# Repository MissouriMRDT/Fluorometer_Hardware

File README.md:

# Fluorometer_Breakout_Hardware
Breakout board for CCD with serial interface

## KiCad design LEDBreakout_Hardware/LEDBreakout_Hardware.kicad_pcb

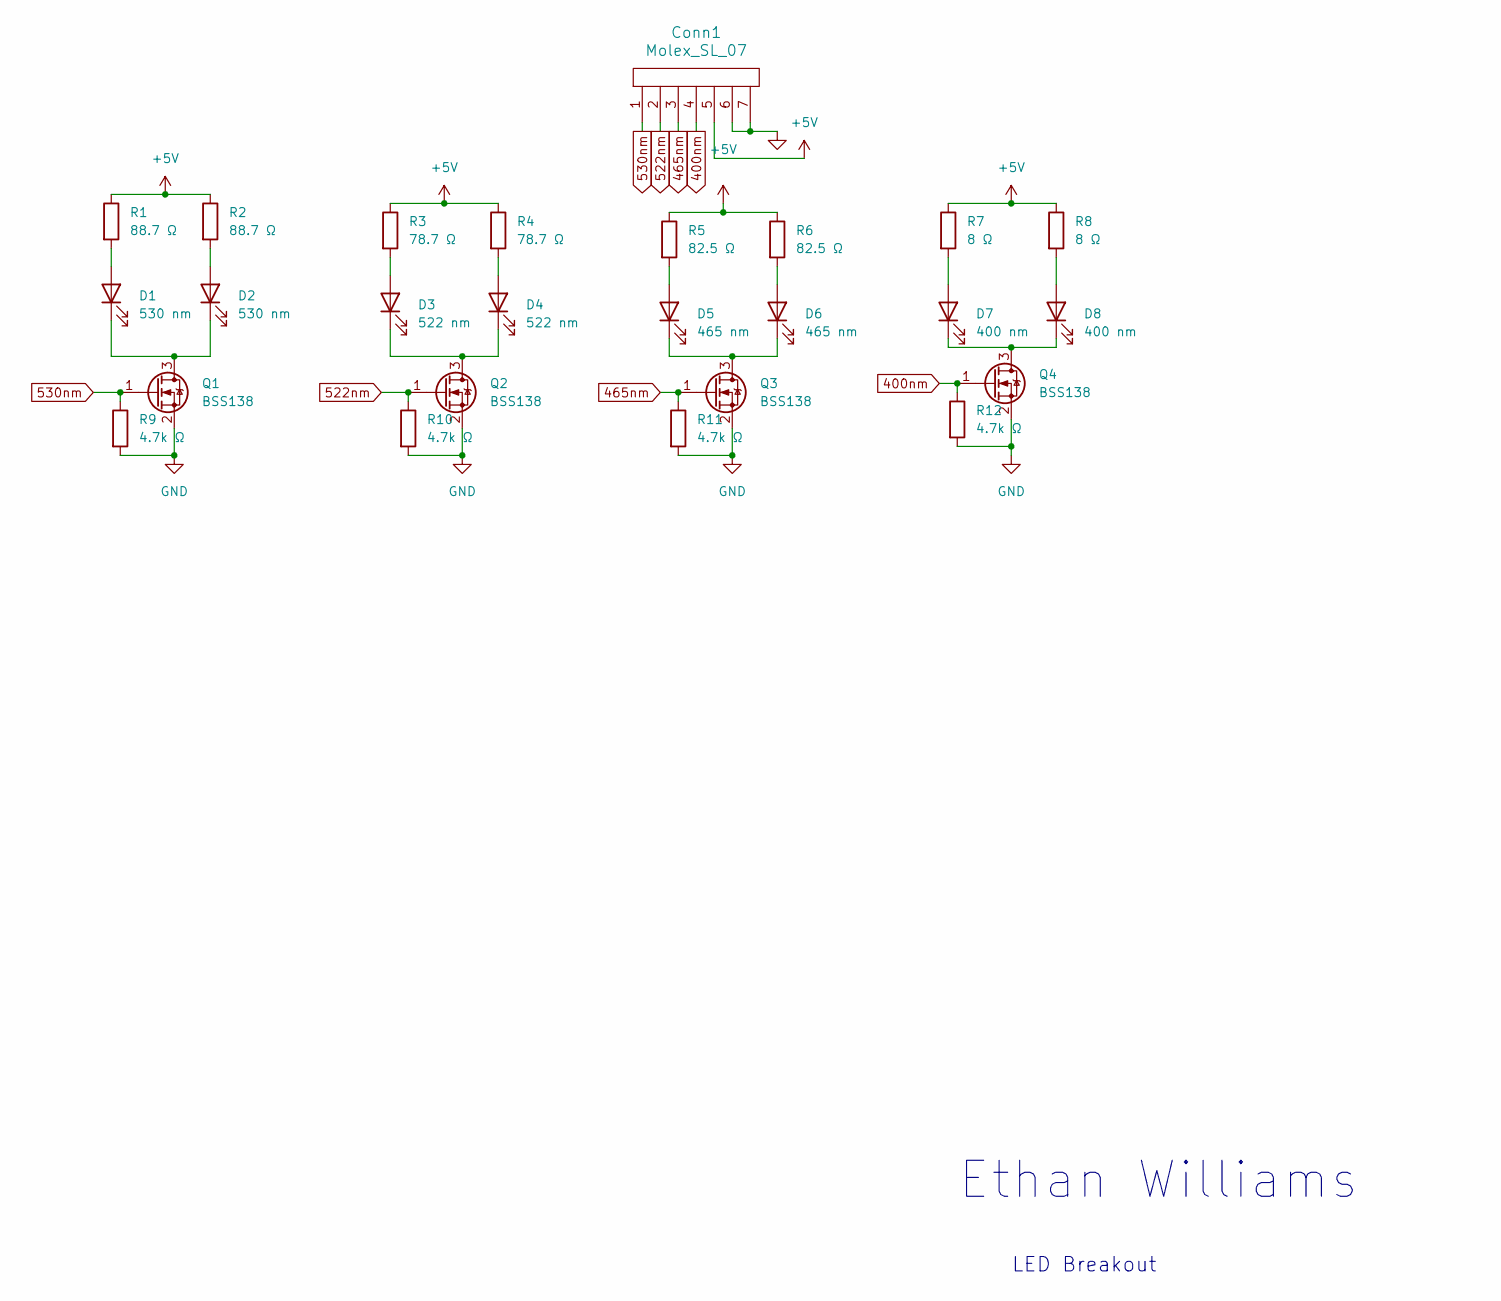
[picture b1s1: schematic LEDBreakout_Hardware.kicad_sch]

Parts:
Conn1: Molex_SL_07; MOLEX_SL_07_Vertical
D1, D2: 530 nm; D_DO-15_P2.54mm_Vertical_AnodeUp
D3, D4: 522 nm; D_DO-15_P2.54mm_Vertical_AnodeUp
D5, D6: 465 nm; D_DO-15_P2.54mm_Vertical_AnodeUp
D7, D8: 400 nm; 3528SMD_Diode
Q1, Q2, Q3, Q4: BSS138; SOT-23
R1, R2: 88.7 Ω; R_0603_1608Metric_Pad0.98x0.95mm_HandSolder
R3, R4: 78.7 Ω; R_0603_1608Metric_Pad0.98x0.95mm_HandSolder
R5, R6: 82.5 Ω; R_0603_1608Metric_Pad0.98x0.95mm_HandSolder
R7, R8: 8 Ω; R_2010_5025Metric_Pad1.40x2.65mm_HandSolder
R9, R10, R11, R12: 4.7k Ω; R_0603_1608Metric_Pad0.98x0.95mm_HandSolder

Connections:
400nm: Conn1.4, Q4.1 (G), R12.1
465nm: Conn1.3, Q3.1 (G), R11.1
522nm: Conn1.2, Q2.1 (G), R10.1
530nm: Conn1.1, Q1.1 (G), R9.1
+5V: Conn1.5, R1.1, R2.1, R3.1, R4.1, R5.1, R6.1, R7.1, R8.1
GND: Conn1.6, Conn1.7, Q1.2 (S), Q2.2 (S), Q3.2 (S), Q4.2 (S), R9.2, R10.2, R11.2, R12.2
unnamed: D1.2 (A), R1.2
unnamed: D1.1 (K), D2.1 (K), Q1.3 (D)
unnamed: D2.2 (A), R2.2
unnamed: D3.2 (A), R3.2
unnamed: D3.1 (K), D4.1 (K), Q2.3 (D)
unnamed: D4.2 (A), R4.2
unnamed: D5.2 (A), R5.2
unnamed: D5.1 (K), D6.1 (K), Q3.3 (D)
unnamed: D6.2 (A), R6.2
unnamed: D7.2 (A), R7.2
unnamed: D7.1 (K), D8.1 (K), Q4.3 (D)
unnamed: D8.2 (A), R8.2

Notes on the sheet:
LED Breakout
Ethan Williams

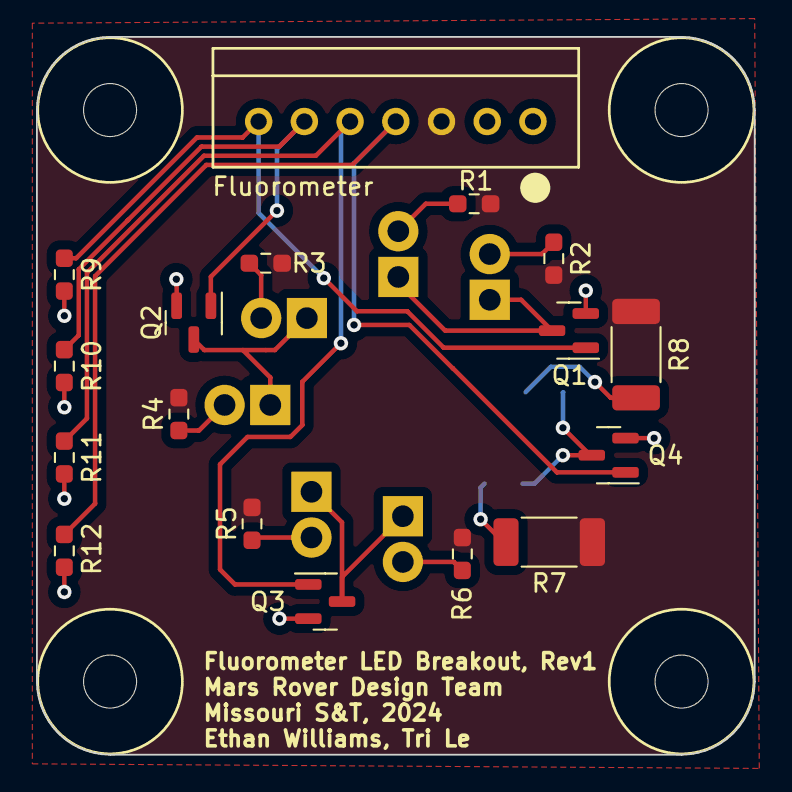
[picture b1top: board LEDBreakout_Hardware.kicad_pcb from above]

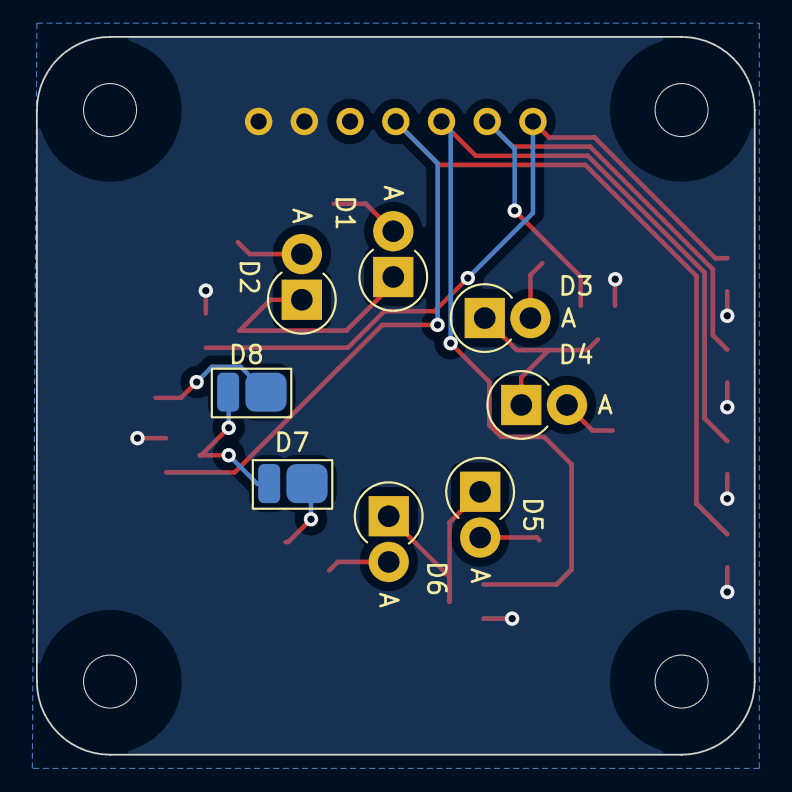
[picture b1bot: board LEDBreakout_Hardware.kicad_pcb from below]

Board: 2 copper layers, 39.9 x 39.9 mm, 25 parts (8 on the bottom side), 18 nets.

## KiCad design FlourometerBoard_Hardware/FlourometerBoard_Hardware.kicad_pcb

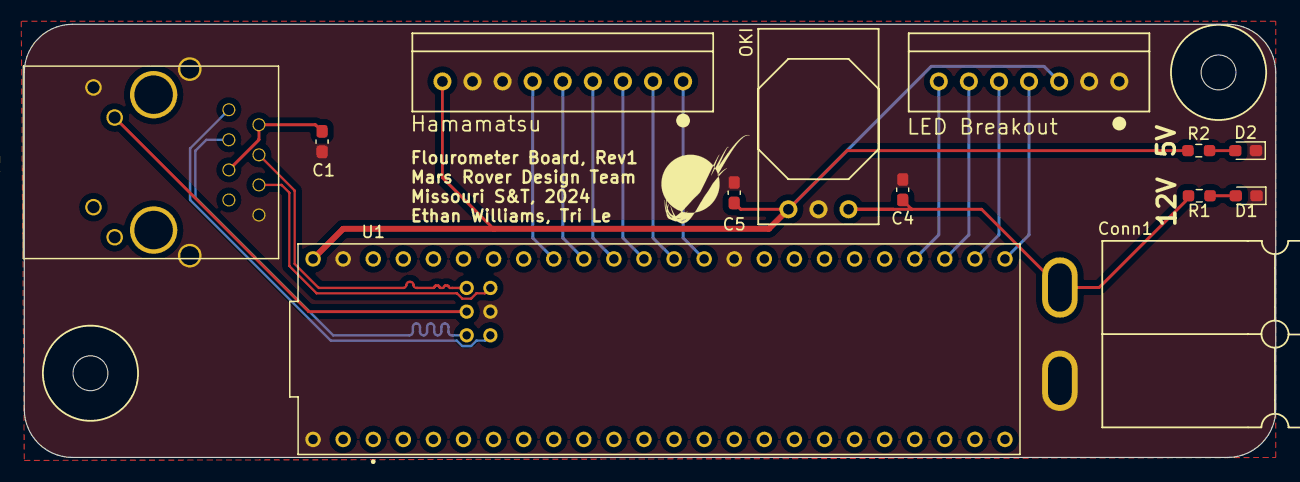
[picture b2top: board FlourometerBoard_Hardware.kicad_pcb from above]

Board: 2 copper layers, 105.7 x 36.6 mm, 13 parts (0 on the bottom side), 21 nets.

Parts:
C1: 0.1 uF; C_0603_1608Metric_Pad1.08x0.95mm_HandSolder
C4, C5: 10 uF; C_0603_1608Metric_Pad1.08x0.95mm_HandSolder
Conn1: AndersonPP; Square_Anderson_2_H_Side_By_Side
Conn2: Molex_SL_09; MOLEX_SL_09_Vertical
Conn3: Molex_SL_07; MOLEX_SL_07_Vertical
D1, D2: Green; LED_0603_1608Metric_Pad1.05x0.95mm_HandSolder
J1: RJ45_LED_Shielded; RJ45_Teensy
R1: 1000 Ω; R_0603_1608Metric_Pad0.98x0.95mm_HandSolder
R2: 100 Ω; R_0603_1608Metric_Pad0.98x0.95mm_HandSolder
U1: Teensy4.1_DEV-16771; Teensy_4_1_Ethernet
U3: OKI; OKI_Horizontal

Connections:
400nm LED: Conn3.4, U1.33 (MCLK2)
430nm LED: Conn3.3, U1.34 (RX8)
522nm LED: Conn3.2, U1.35 (TX8)
530nm LED: Conn3.1, U1.36 (CS2)
+5V: C5.1, Conn2.1, Conn3.5, R2.1, U1.VIN, U3.3 (Vo)
+12V: C4.1, Conn1.2 (V+Log), R1.1, U3.1 (Vi)
CLK: Conn2.7, U1.15 (A1)
EOS: Conn2.4, U1.18 (A4)
GND: C1.1, C4.2, C5.2, Conn1.1 (GND), Conn2.2, Conn2.3, Conn3.6, Conn3.7, D1.1 (K), D2.1 (K), J1.8, J1.9, J1.SH, U1.GND1 (GND), U1.GND2 (GND), U1.GND3 (GND), U1.GND5 (GND), U3.2 (GND)
LED: J1.10, U1.LED
unnamed: C1.2, J1.2, J1.5
unnamed: D1.2 (A), R1.2
unnamed: D2.2 (A), R2.2
R+: J1.4, U1.R+
R-: J1.6, U1.R-
START: Conn2.6, U1.16 (A2)
T+: J1.1, U1.T+
T-: J1.3, U1.T-
TRG: Conn2.5, U1.17 (A3)
VIDEO: Conn2.8, U1.14 (A0)
WHITE_LED: Conn2.9, U1.13 (SCK)

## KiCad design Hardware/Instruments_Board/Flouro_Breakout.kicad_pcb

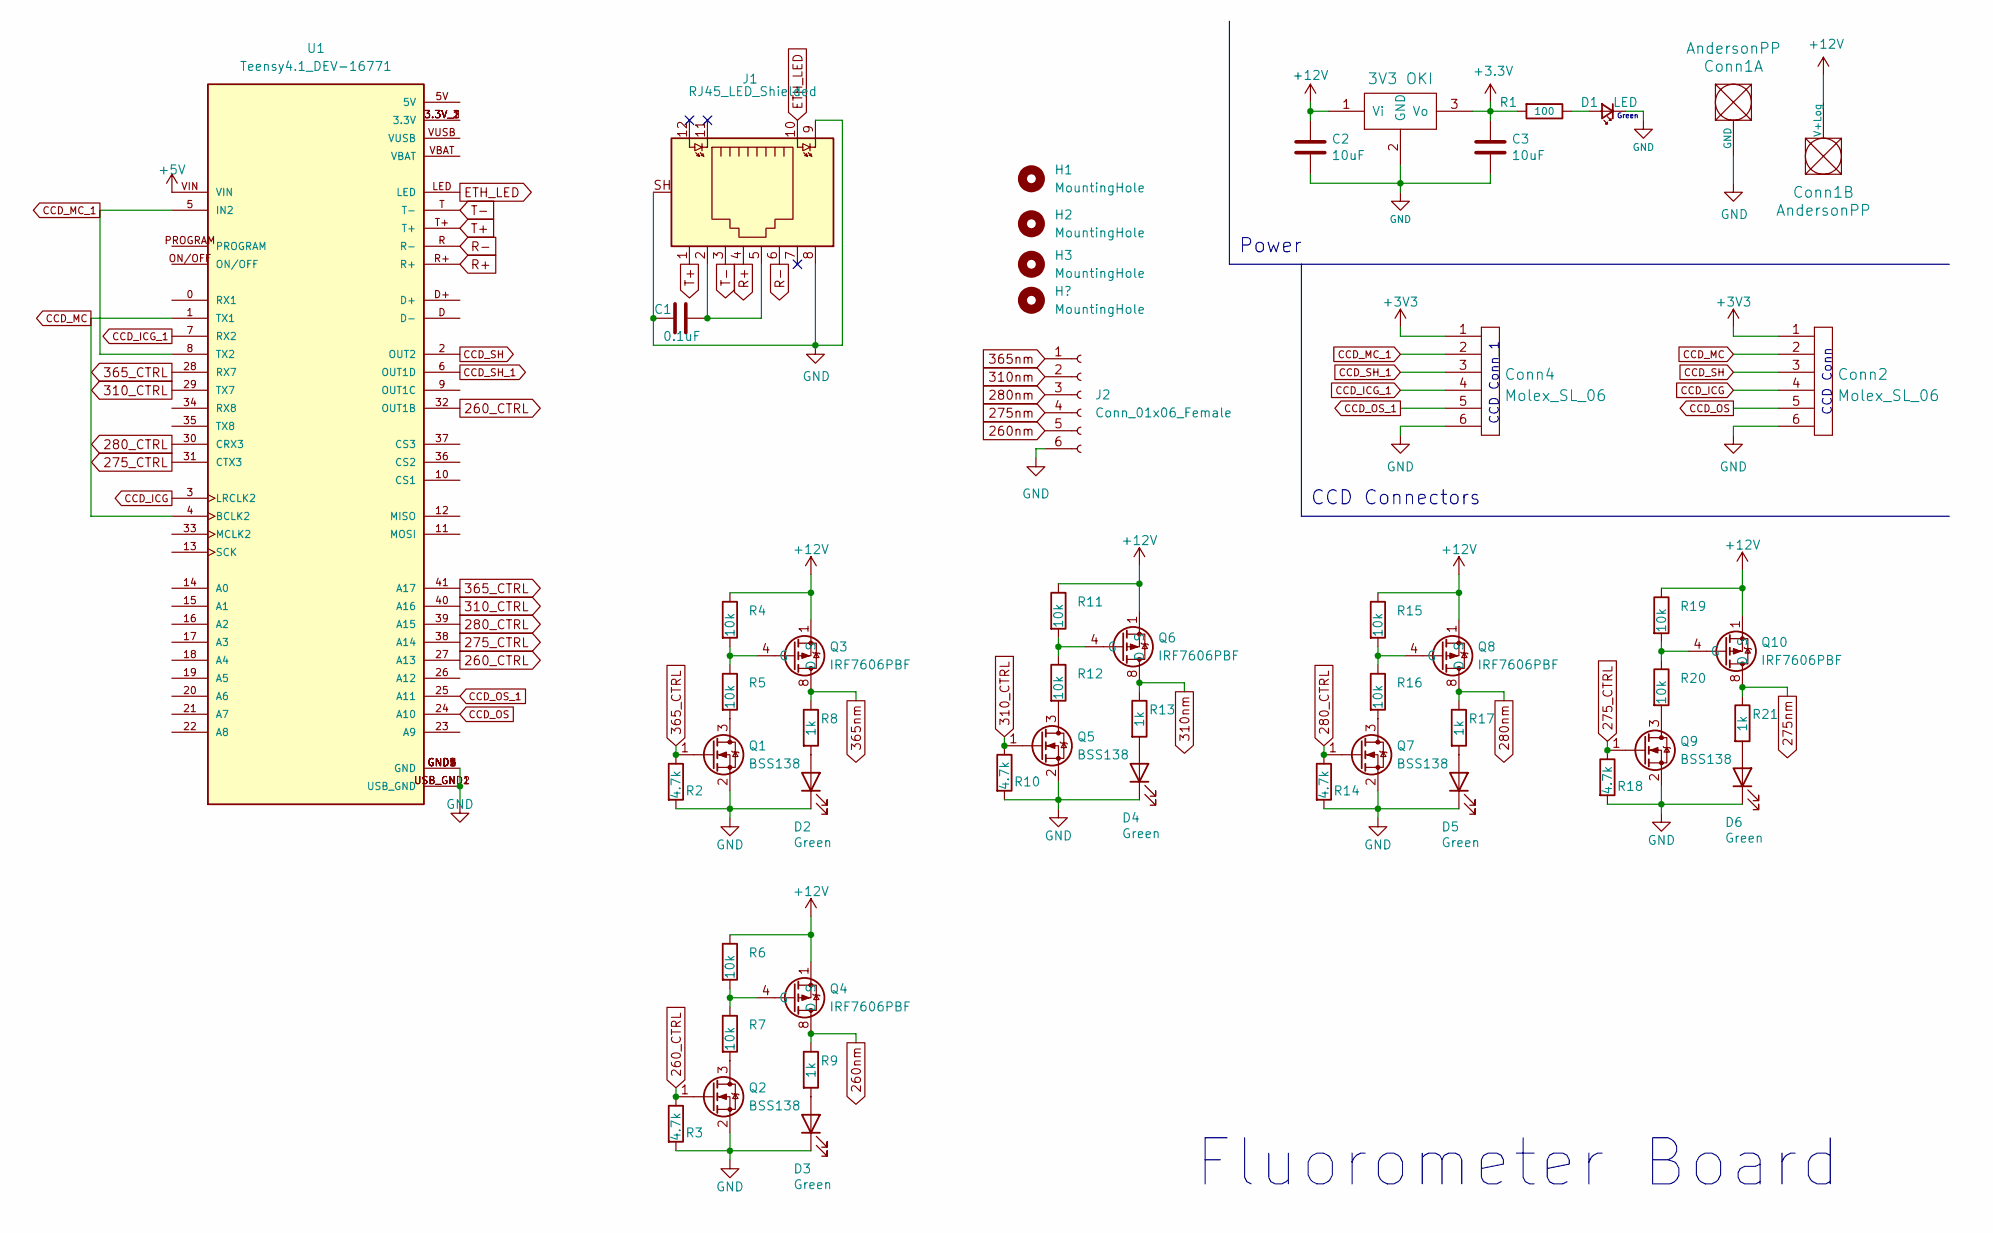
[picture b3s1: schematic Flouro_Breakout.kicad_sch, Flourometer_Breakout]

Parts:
C1: 0.1uF; C_0603_1608Metric_Pad1.08x0.95mm_HandSolder
C2, C3: 10uF; C_0603_1608Metric_Pad1.08x0.95mm_HandSolder
Conn1: AndersonPP; Square_Anderson_2_H_Side_By_Side
Conn2, Conn4: Molex_SL_06; Molex_SL_171971-0006_1x06_P2.54mm_Vertical
D1: LED; LED_0603_1608Metric_Pad1.05x0.95mm_HandSolder
D2, D3, D4, D5, D6: Green; LED_0603_1608Metric_Pad1.05x0.95mm_HandSolder
H1, H2, H3: MountingHole; 4_40_Hole_Corner
J1: RJ45_LED_Shielded; RJ45_Teensy
J2: Conn_01x06_Female; Molex_SL_171971-0006_1x06_P2.54mm_Vertical
Q1, Q2, Q5, Q7, Q9: BSS138; SOT-23
Q3, Q4, Q6, Q8, Q10: IRF7606PBF; SOP-8_3.9x4.9mm_P1.27mm
R1: 100; R_0603_1608Metric_Pad0.98x0.95mm_HandSolder
R2, R3, R10, R14, R18: 4.7k; R_0603_1608Metric_Pad0.98x0.95mm_HandSolder
R4, R5, R6, R7, R11, R12, R15, R16, R19, R20: 10k; R_0603_1608Metric_Pad0.98x0.95mm_HandSolder
R8, R9, R13, R17, R21: 1k; R_0603_1608Metric_Pad0.98x0.95mm_HandSolder
U1: Teensy4.1_DEV-16771; Teensy_4_1; PARTREV 4.1
U2: 3V3 OKI; OKI_Horizontal

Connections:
260_CTRL: Q2.1 (G), R3.1, U1.27 (A13), U1.32 (OUT1B)
260nm: J2.5, Q4.5 (D), Q4.6 (D), Q4.7 (D), Q4.8 (D), R9.1
275_CTRL: Q9.1 (G), R18.1, U1.31 (CTX3), U1.38 (A14)
275nm: J2.4, Q10.5 (D), Q10.6 (D), Q10.7 (D), Q10.8 (D), R21.1
280_CTRL: Q7.1 (G), R14.1, U1.30 (CRX3), U1.39 (A15)
280nm: J2.3, Q8.5 (D), Q8.6 (D), Q8.7 (D), Q8.8 (D), R17.1
310_CTRL: Q5.1 (G), R10.1, U1.29 (TX7), U1.40 (A16)
310nm: J2.2, Q6.5 (D), Q6.6 (D), Q6.7 (D), Q6.8 (D), R13.1
365_CTRL: Q1.1 (G), R2.1, U1.28 (RX7), U1.41 (A17)
365nm: J2.1, Q3.5 (D), Q3.6 (D), Q3.7 (D), Q3.8 (D), R8.1
CCD_SH_1: Conn4.3, U1.6 (OUT1D)
+3.3V: C3.1, R1.2, U2.3 (Vo)
+3V3: Conn2.1, Conn4.1
+5V: U1.VIN
+12V: C2.1, Conn1.2 (V+Log), Q3.1 (S), Q3.2 (S), Q3.3 (S), Q4.1 (S), Q4.2 (S), Q4.3 (S), Q6.1 (S), Q6.2 (S), Q6.3 (S), Q8.1 (S), Q8.2 (S), Q8.3 (S), Q10.1 (S), Q10.2 (S), Q10.3 (S), R4.1, R6.1, R11.1, R15.1, R19.1, U2.1 (Vi)
CCD_ICG: Conn2.4, U1.3 (LRCLK2)
CCD_ICG_1: Conn4.4, U1.7 (RX2)
CCD_MC: Conn2.2, U1.1 (TX1), U1.4 (BCLK2)
CCD_MC_1: Conn4.2, U1.5 (IN2), U1.8 (TX2)
CCD_OS: Conn2.5, U1.24 (A10)
CCD_OS_1: Conn4.5, U1.25 (A11)
CCD_SH: Conn2.3, U1.2 (OUT2)
ETH_LED: J1.10, U1.LED
GND: C1.2, C2.2, C3.2, Conn1.1 (GND), Conn2.6, Conn4.6, D1.1 (K), D2.1 (K), D3.1 (K), D4.1 (K), D5.1 (K), D6.1 (K), J1.8, J1.9, J1.SH, J2.6, Q1.2 (S), Q2.2 (S), Q5.2 (S), Q7.2 (S), Q9.2 (S), R2.2, R3.2, R10.2, R14.2, R18.2, U1.GND1 (GND), U1.GND2 (GND), U1.GND3 (GND), U1.GND4 (GND), U1.GND5 (GND), U1.USB_GND1 (USB_GND), U1.USB_GND2 (USB_GND), U2.2 (GND)
unnamed: C1.1, J1.2, J1.5
unnamed: D1.2 (A), R1.1
unnamed: D2.2 (A), R8.2
unnamed: D3.2 (A), R9.2
unnamed: D4.2 (A), R13.2
unnamed: D5.2 (A), R17.2
unnamed: D6.2 (A), R21.2
unnamed: Q1.3 (D), R5.2
unnamed: Q2.3 (D), R7.2
unnamed: Q3.4 (G), R4.2, R5.1
unnamed: Q4.4 (G), R6.2, R7.1
unnamed: Q5.3 (D), R12.2
unnamed: Q6.4 (G), R11.2, R12.1
unnamed: Q7.3 (D), R16.2
unnamed: Q8.4 (G), R15.2, R16.1
unnamed: Q9.3 (D), R20.2
unnamed: Q10.4 (G), R19.2, R20.1
unnamed: U1.3.3V_1 (3.3V), U1.3.3V_2 (3.3V), U1.3.3V_3 (3.3V)
R+: J1.4, U1.R+
R-: J1.6, U1.R (R-)
T+: J1.1, U1.T+
T-: J1.3, U1.T (T-)

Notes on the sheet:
Fluorometer Board
Green
Power
CCD Conn
CCD Conn_1
CCD Connectors

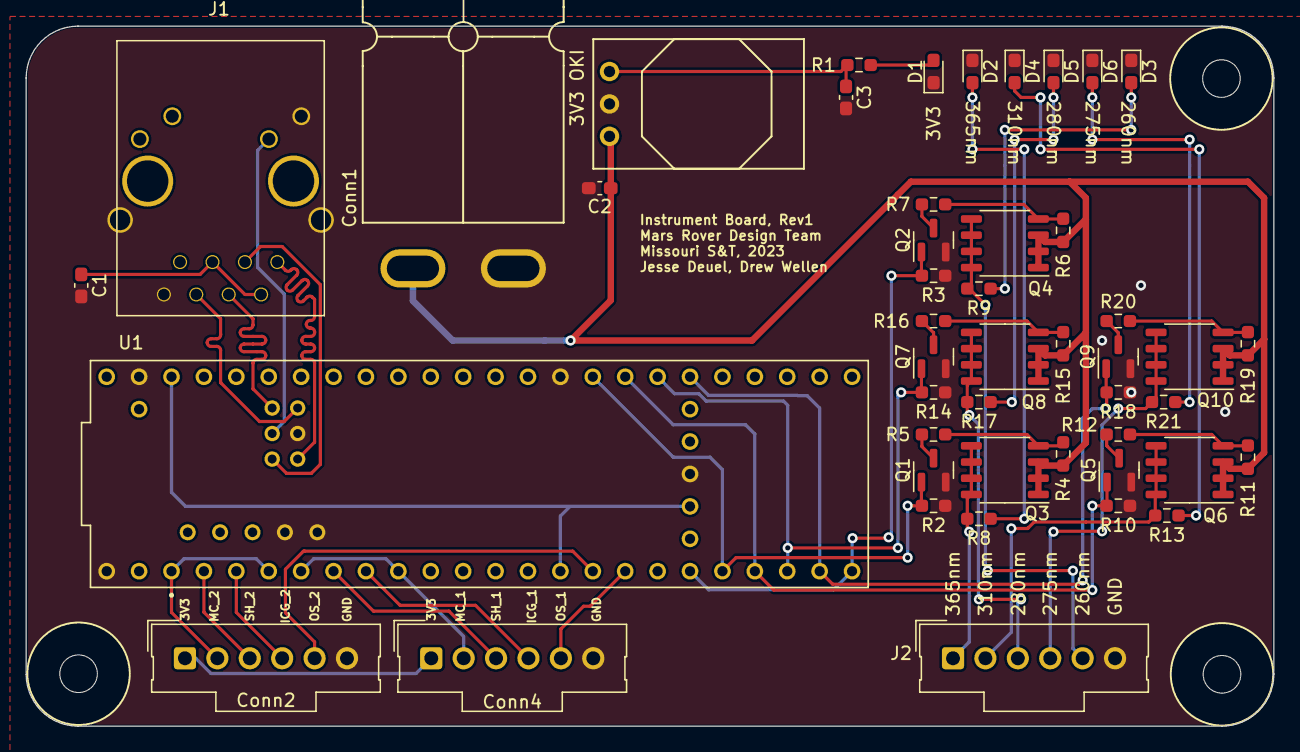
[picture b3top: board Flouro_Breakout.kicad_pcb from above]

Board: 2 copper layers, 97.8 x 54.9 mm, 50 parts (0 on the bottom side), 43 nets.

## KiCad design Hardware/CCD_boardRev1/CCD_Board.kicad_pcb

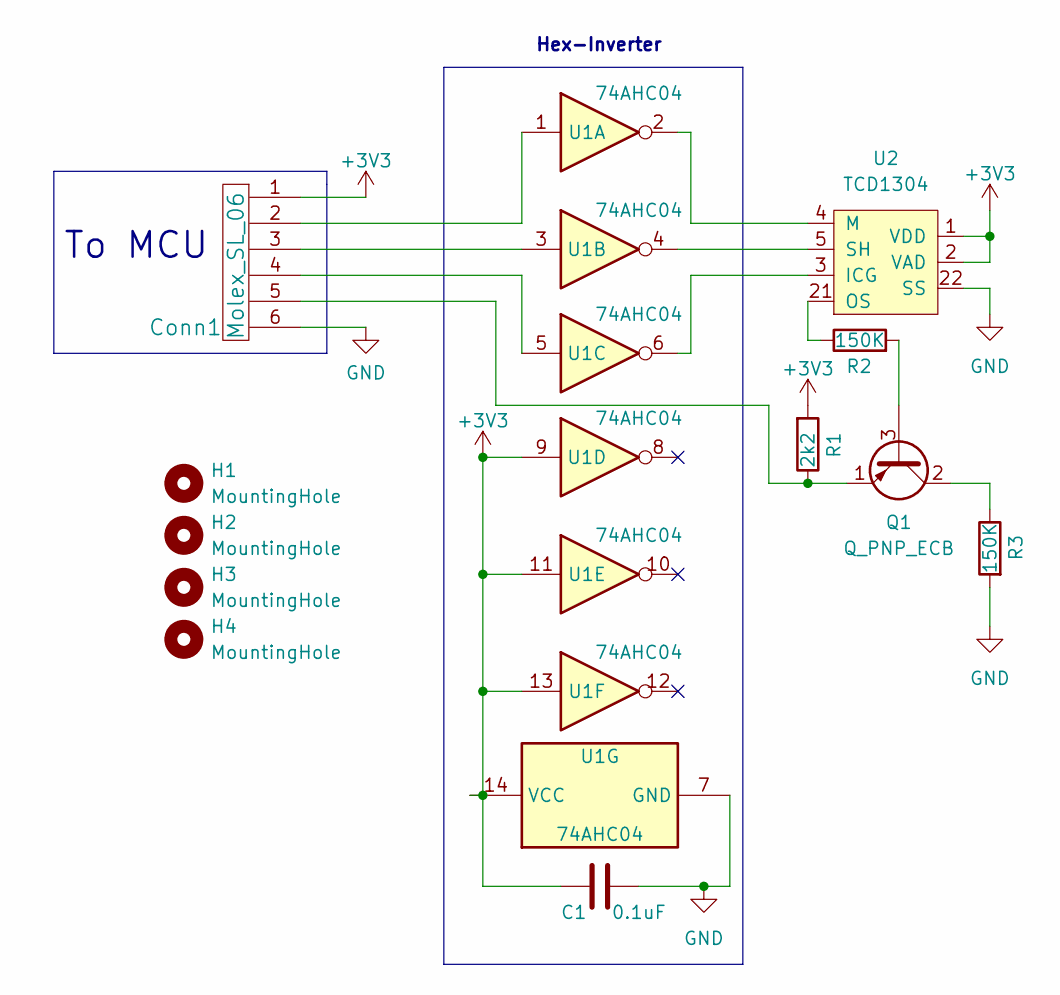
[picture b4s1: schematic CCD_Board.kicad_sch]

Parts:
C1: 0.1uF; C_0603_1608Metric
Conn1: Molex_SL_06; Molex_SL_171971-0006_1x06_P2.54mm_Vertical
H1, H2, H3, H4: MountingHole; 4_40_Hole_Corner
Q1: Q_PNP_ECB; TO-92
R1: 2k2; R_0603_1608Metric
R2, R3: 150K; R_0603_1608Metric
U1: 74AHC04; SOIC-14_3.9x8.7mm_P1.27mm
U2: TCD1304; TCD-1304

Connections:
+3V3: C1.2, Conn1.1, R1.2, U1.9, U1.11, U1.13, U1.14 (VCC), U2.1 (VDD), U2.2 (VAD)
GND: C1.1, Conn1.6, R3.2, U1.7 (GND), U2.22 (SS)
unnamed: Conn1.2, U1.1
unnamed: Conn1.3, U1.3
unnamed: Conn1.4, U1.5
unnamed: Conn1.5, Q1.1 (E), R1.1
unnamed: Q1.2 (C), R3.1
unnamed: Q1.3 (B), R2.2
unnamed: R2.1, U2.21 (OS)
unnamed: U1.2, U2.4 (M)
unnamed: U1.4, U2.5 (SH)
unnamed: U1.6, U2.3 (ICG)

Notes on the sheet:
To MCU
Hex-Inverter

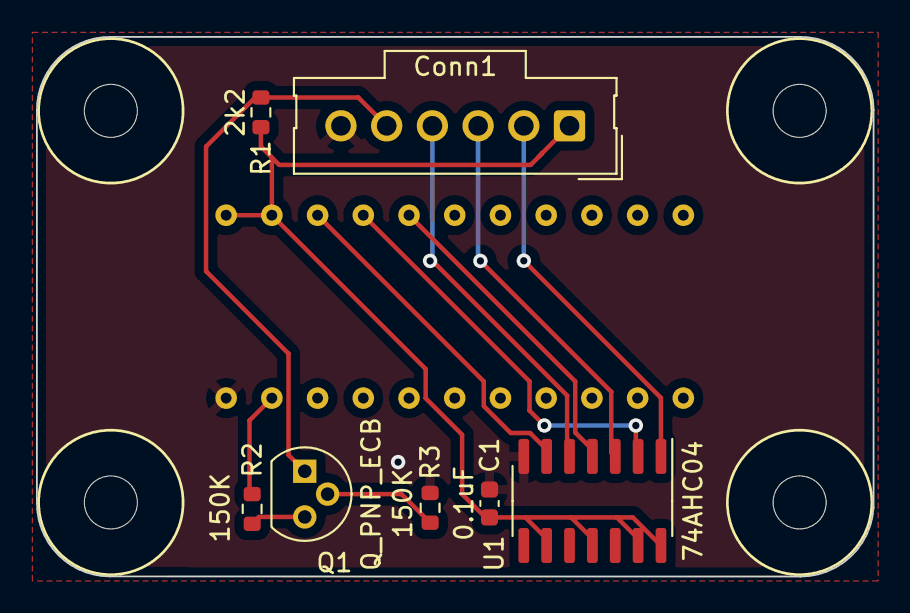
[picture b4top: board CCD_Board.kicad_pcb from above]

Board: 2 copper layers, 46.5 x 30.0 mm, 12 parts (1 on the bottom side), 12 nets.

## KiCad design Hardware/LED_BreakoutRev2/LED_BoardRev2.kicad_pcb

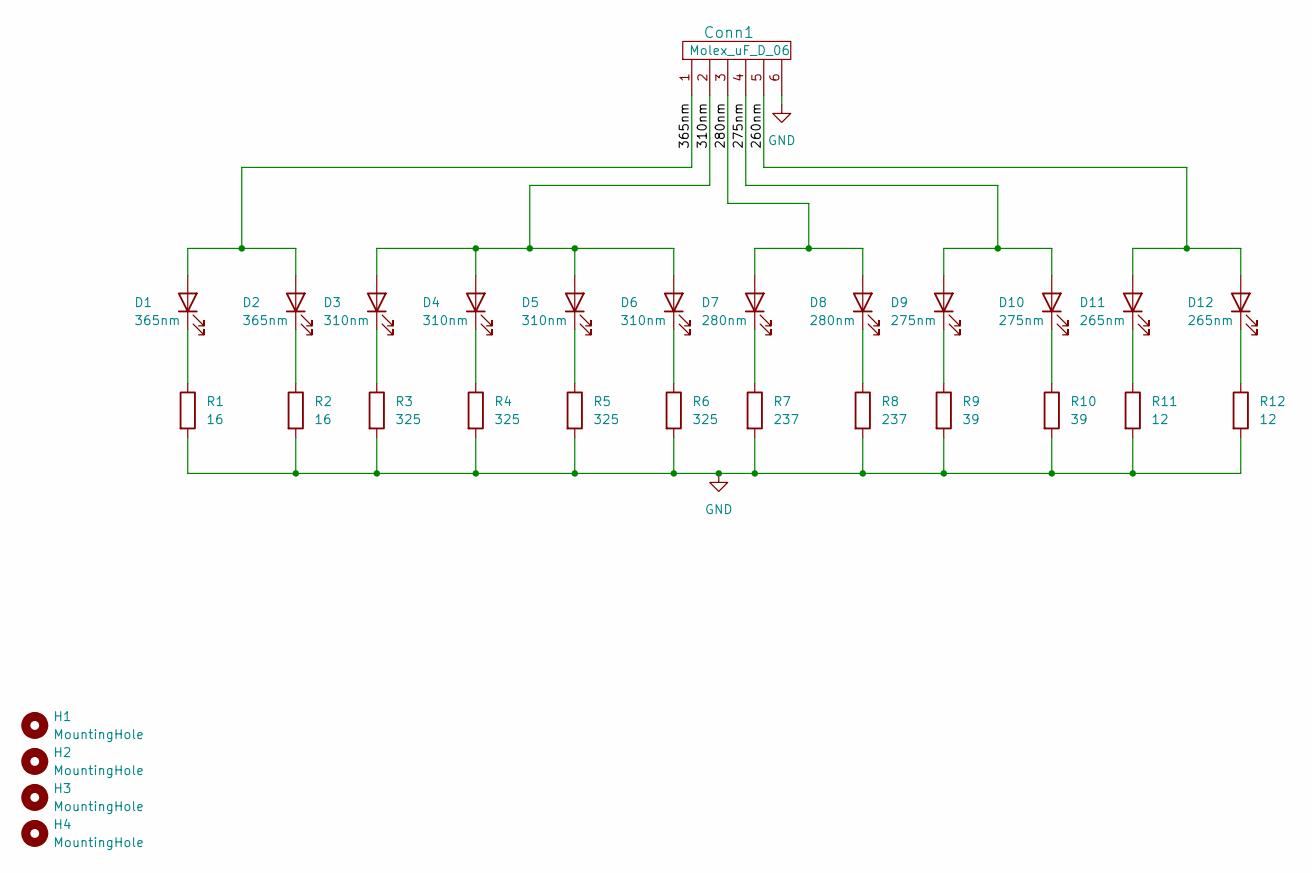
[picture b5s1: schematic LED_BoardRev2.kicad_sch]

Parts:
Conn1: Molex_uF_D_06; Molex_SL_171971-0006_1x06_P2.54mm_Vertical
D1, D2: 365nm; LZ1-00UV0R
D3, D4, D5, D6: 310nm; 1414_3535_Metric
D7, D8: 280nm; VLMU35CL2.-275-120
D9, D10: 275nm; SU CULCN1.VC
D11, D12: 265nm; 1414_3535_Metric
H1, H2, H3, H4: MountingHole; 4_40_Hole_Corner
R1, R2: 16; R_2512_6332Metric_Pad1.40x3.35mm_HandSolder
R3, R4, R5, R6: 325; R_2512_6332Metric_Pad1.40x3.35mm_HandSolder
R7, R8: 237; R_2512_6332Metric_Pad1.40x3.35mm_HandSolder
R9, R10: 39; R_2512_6332Metric_Pad1.40x3.35mm_HandSolder
R11, R12: 12; R_2512_6332Metric_Pad1.40x3.35mm_HandSolder

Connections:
/260nm: Conn1.5, D11.2 (A), D12.2 (A)
/275nm: Conn1.4, D9.2 (A), D10.2 (A)
/280nm: Conn1.3, D7.2 (A), D8.2 (A)
/310nm: Conn1.2, D3.2 (A), D4.2 (A), D5.2 (A), D6.2 (A)
/365nm: Conn1.1, D1.2 (A), D2.2 (A)
GND: Conn1.6, R1.2, R2.2, R3.2, R4.2, R5.2, R6.2, R7.2, R8.2, R9.2, R10.2, R11.2, R12.2
unnamed: D1.1 (K), R1.1
unnamed: D2.1 (K), R2.1
unnamed: D3.1 (K), R3.1
unnamed: D4.1 (K), R4.1
unnamed: D5.1 (K), R5.1
unnamed: D6.1 (K), R6.1
unnamed: D7.1 (K), R7.1
unnamed: D8.1 (K), R8.1
unnamed: D9.1 (K), R9.1
unnamed: D10.1 (K), R10.1
unnamed: D11.1 (K), R11.1
unnamed: D12.1 (K), R12.1

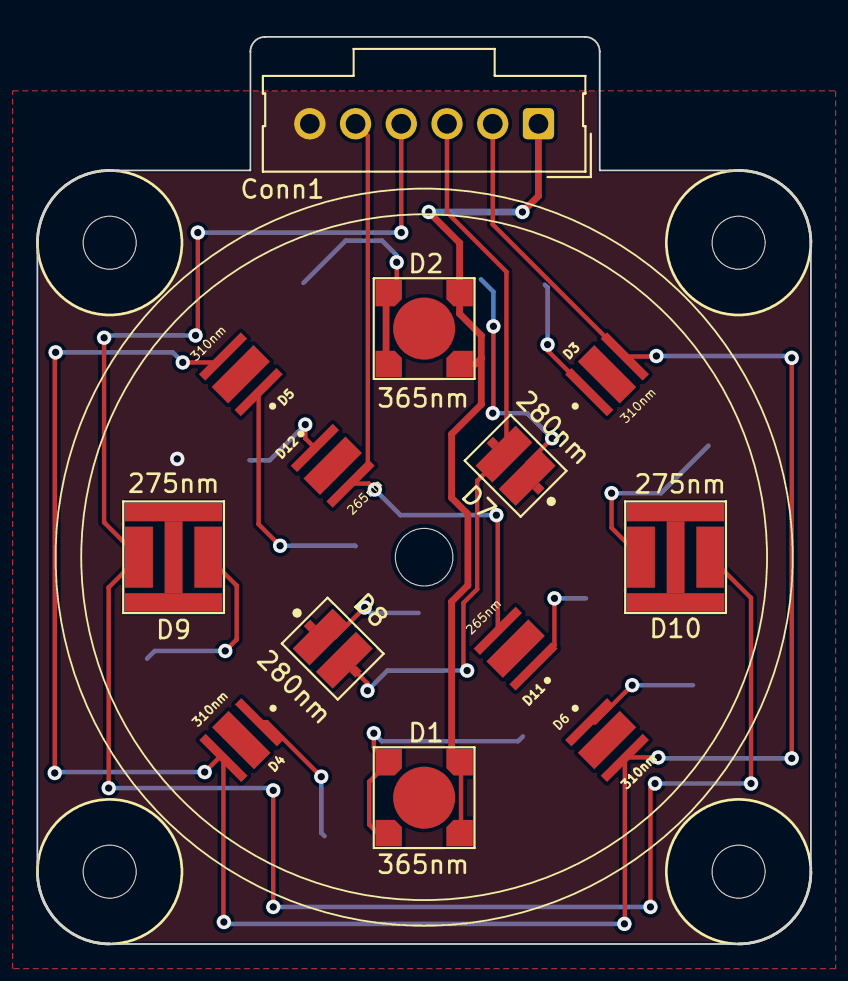
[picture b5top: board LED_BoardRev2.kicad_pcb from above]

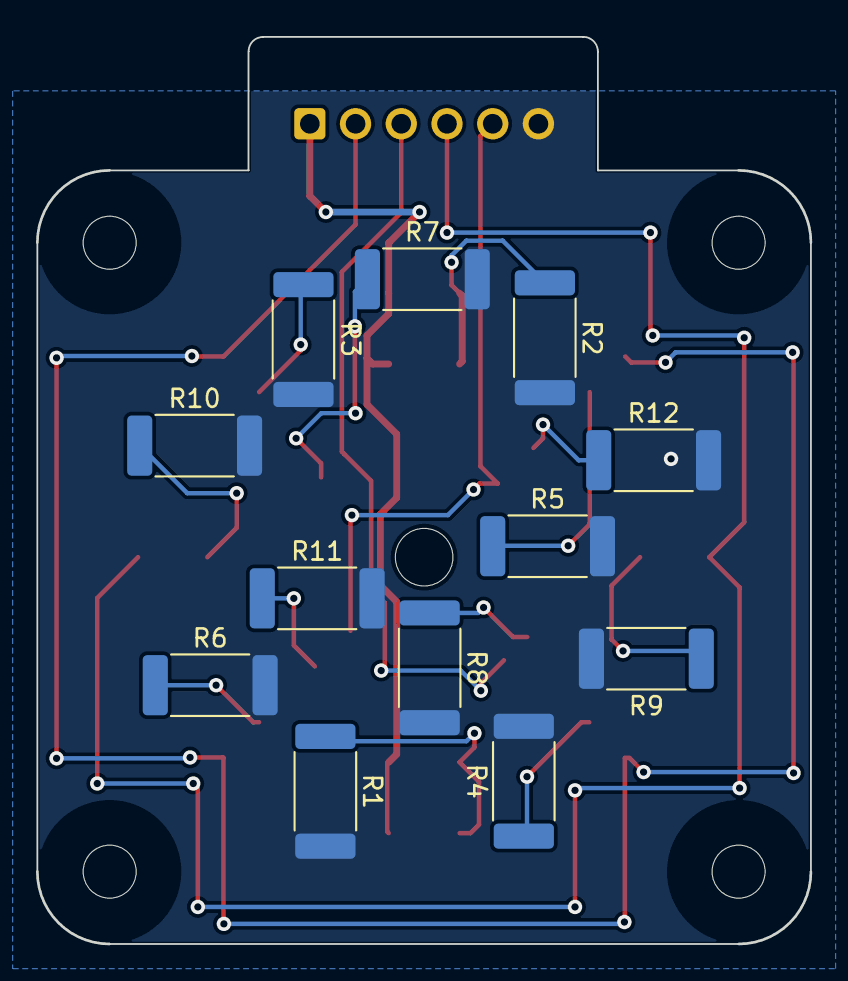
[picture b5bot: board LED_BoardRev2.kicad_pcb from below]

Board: 2 copper layers, 43.0 x 50.4 mm, 29 parts (12 on the bottom side), 18 nets.

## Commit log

2023-03-07 First time page setup
2023-03-08 Added in headers
2023-03-10 Adding more bits
2023-03-11 Added teensy and ethernet
2023-03-11 Made CCD board and LED Rev2 folders
    Starting schematic of CCD board.
2023-03-27 Finished Fluoro-board Schematic
2023-03-28 Finished CCD Board Layout
2023-03-30 Created LED_Rev2 Filepath
2023-03-31 Start LEDRev2
2023-04-09 First draft of LED board Schematic
2023-04-09 Finalizing schematic component placement
2023-04-09 Added power to Fluoro Board
2023-04-10 LED footprints
2023-04-11 New LED Footprints Made
2023-04-15 Added resistor values and LED datasheets
2023-04-15 More Footprints
2023-04-16 re-arranged schematic
2023-04-18 Finished LED Schematic
2023-04-18 Began Layout
2023-04-18 Began future proofing instruments board
2023-04-18 I Forgot
2023-04-20 moved footprints to libraries folder
2023-04-21 adjusted resistor values
2023-04-21 Fixed resistor values
2023-04-21 Update datasheet
2023-04-21 Edit footprint
2023-04-21 Added 275 nm LED footprint
2023-04-21 Concept LED layout
2023-04-21 Still moving footprints
2023-04-21 Finished 365 nm led footprint
2023-04-21 Update fp-info-cache
2023-04-21 LED Footprints
    280 nm
    265 nm
    310 nm
2023-04-21 Closed kicad
2023-04-21 Changing layout
2023-04-22 Change backups
2023-04-22 Editing LED placement
2023-04-22 Fixed things grant suggested
2023-04-22 Moving MOSFTETs over to instruments board
2023-04-22 Running traces
2023-04-22 Finished LED Board Rev2
2023-04-22 Compressed Gerbs
2023-04-22 Gerbs...
2023-04-22 finished fluoro breakout
2023-04-22 Finished with signatures and headers
2023-04-22 geeeeeerbs
2023-04-22 info-cache
2023-04-22 updated mounting holes
2023-05-03 Made STEP files
2023-05-22 page edits for printing
2023-05-23 Nothing
2023-09-21 Created Fluro Board Schematic
2023-09-25 Boxed and Labeled Circuits
2023-09-26 Update Board According to Schematic Review
2023-09-29 Organized Schematic, Changed Anderson to V+Log
2023-09-29 Organized Schematic, added 12V to 3V3 converter
2023-09-29 Created LED Breakout Project in KiCad
2023-09-29 Changed Fluoro Connector to Molex, Changed Buck to 3V3
2023-09-29 Re-Created LED Breakout Project
2023-09-29 Added Molex and LEDs
2023-10-04 Began Layout, Updated Footprint
2023-10-04 Finished routing all traces on layout
2023-10-04 Initial Fluoro Board Layout Complete
2023-10-12 Added Resistors to LED Breakout
2023-10-13 Added LED Breakout Connector to Fluoro Board
    Also updated footprint for both boards
2023-10-13 Started LED Layout
2023-10-15 Added 5V to LED connectors
    Also added FETs to LEDs on breakout.
2023-10-15 Added Traces for LED Breakout
2023-10-16 Changes made based on layout review notes
2023-10-17 Finished LED Breakout Layout
2023-10-17 Changed Anderson Footprint from PV
2023-10-17 Rearranged Silkscreen Labels
2023-10-17 Added Pull Down Resistors to MOSFETs
    And some other things
2023-10-31 Complied with most of CDR changes
2023-10-31 Finished Main Board Secondary Notes
2023-10-31 Finished LED Breakout
2023-11-01 Moved Vias off pads
2023-11-02 Moved Vias
2023-11-03 Final Revisions
2023-11-03 Revert "Final Revisions"
    This reverts commit 08823e9a4bc57385ed17316fa6c40b2b69caaa08.
2023-11-03 Final Revisions Part 2
2023-11-05 Created Gerber Files
2023-11-05 Created Gerber Files for LED Breakout
2023-11-05 Center diodes and regenerate Gerbs
